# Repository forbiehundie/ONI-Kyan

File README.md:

# ONI-Kyan
A smol 30% columnar stagger keyboard designed to be used with a Pro-Micro and compatibles. 

ONI-Kyan MKI; mx only

ONI-Kyan Shakotan MKI; choc only with choc specific switch spacing

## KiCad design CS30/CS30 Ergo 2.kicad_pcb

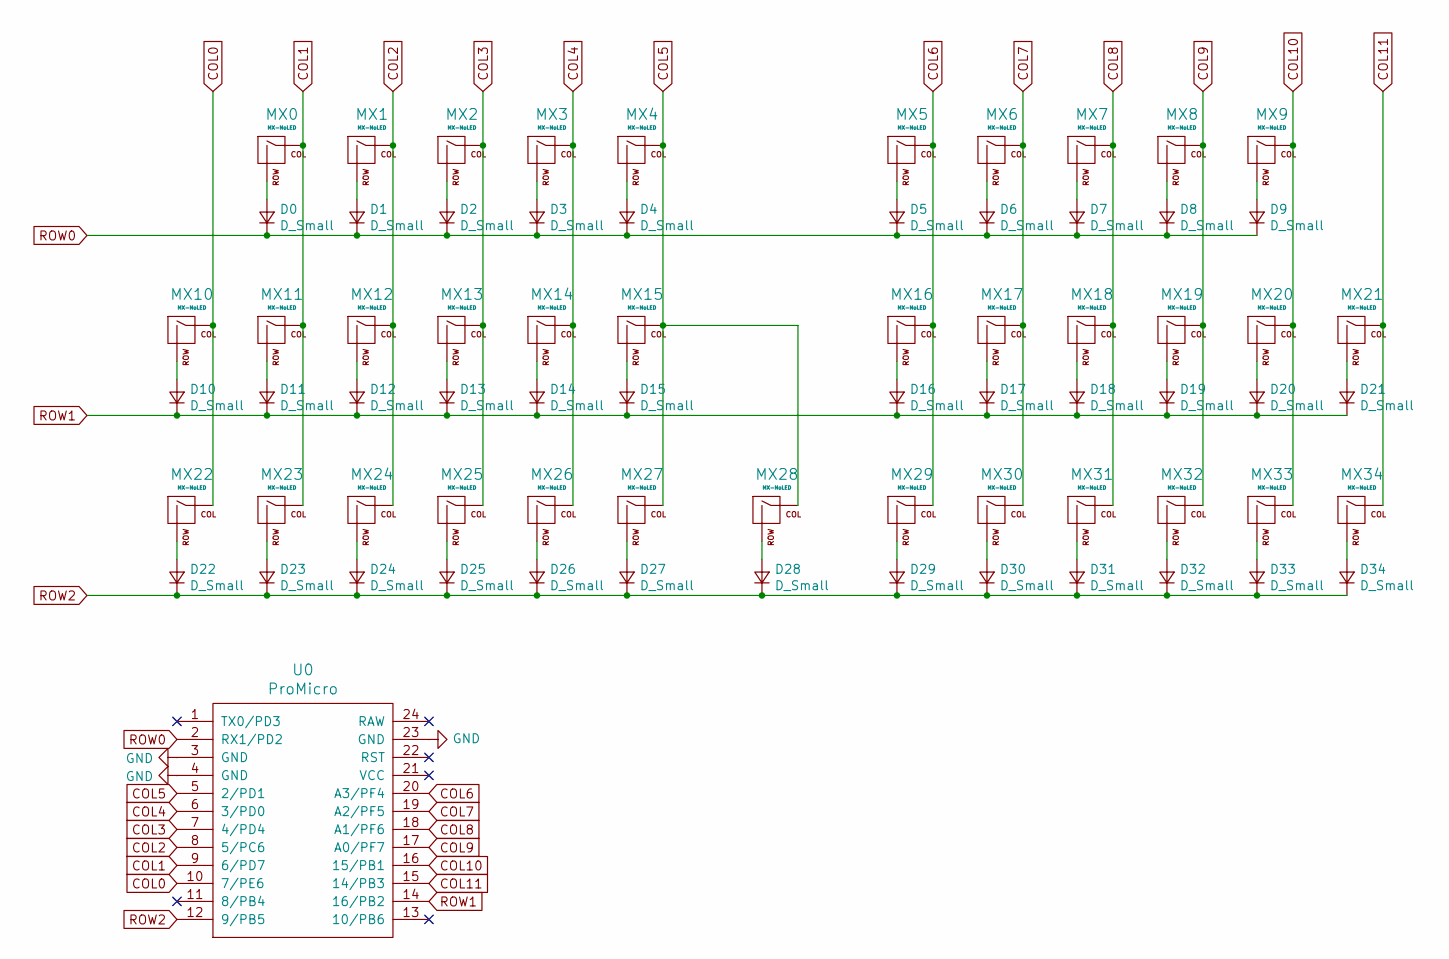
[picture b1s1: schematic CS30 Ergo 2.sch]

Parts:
D0, D1, D2, D3, D4, D5, D6, D7, D8, D9, D10, D11, D12, D13, D14, D15, D16, D17, D18, D19, D20, D21, D22, D23, D24, D25, D26, D27, D28, D29, D30, D31, D32, D33, D34: D_Small; D_SOD-123-Pretty
MX0, MX1, MX2, MX3, MX4, MX5, MX6, MX7, MX8, MX9, MX10, MX11, MX12, MX13, MX14, MX15, MX16, MX17, MX18, MX19, MX20, MX21, MX22, MX23, MX24, MX25, MX26, MX27, MX29, MX30, MX31, MX32, MX33, MX34: MX-NoLED; MXOnly-1U-NoLED
MX28: MX-NoLED; MXOnly-1.25U-NoLED
U0: ProMicro; ArduinoProMicro

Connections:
COL0: MX10.1 (COL), MX22.1 (COL), U0.10 (7/PE6)
COL1: MX0.1 (COL), MX11.1 (COL), MX23.1 (COL), U0.9 (6/PD7)
COL2: MX1.1 (COL), MX12.1 (COL), MX24.1 (COL), U0.8 (5/PC6)
COL3: MX2.1 (COL), MX13.1 (COL), MX25.1 (COL), U0.7 (4/PD4)
COL4: MX3.1 (COL), MX14.1 (COL), MX26.1 (COL), U0.6 (3/PD0)
COL5: MX4.1 (COL), MX15.1 (COL), MX27.1 (COL), MX28.1 (COL), U0.5 (2/PD1)
COL6: MX5.1 (COL), MX16.1 (COL), MX29.1 (COL), U0.20 (A3/PF4)
COL7: MX6.1 (COL), MX17.1 (COL), MX30.1 (COL), U0.19 (A2/PF5)
COL8: MX7.1 (COL), MX18.1 (COL), MX31.1 (COL), U0.18 (A1/PF6)
COL9: MX8.1 (COL), MX19.1 (COL), MX32.1 (COL), U0.17 (A0/PF7)
COL10: MX9.1 (COL), MX20.1 (COL), MX33.1 (COL), U0.16 (15/PB1)
COL11: MX21.1 (COL), MX34.1 (COL), U0.15 (14/PB3)
GND: U0.3 (GND), U0.4 (GND), U0.23 (GND)
unnamed: D0.2 (A), MX0.2 (ROW)
unnamed: D1.2 (A), MX1.2 (ROW)
unnamed: D2.2 (A), MX2.2 (ROW)
unnamed: D3.2 (A), MX3.2 (ROW)
unnamed: D4.2 (A), MX4.2 (ROW)
unnamed: D5.2 (A), MX5.2 (ROW)
unnamed: D6.2 (A), MX6.2 (ROW)
unnamed: D7.2 (A), MX7.2 (ROW)
unnamed: D8.2 (A), MX8.2 (ROW)
unnamed: D9.2 (A), MX9.2 (ROW)
unnamed: D10.2 (A), MX10.2 (ROW)
unnamed: D11.2 (A), MX11.2 (ROW)
unnamed: D12.2 (A), MX12.2 (ROW)
unnamed: D13.2 (A), MX13.2 (ROW)
unnamed: D14.2 (A), MX14.2 (ROW)
unnamed: D15.2 (A), MX15.2 (ROW)
unnamed: D16.2 (A), MX16.2 (ROW)
unnamed: D17.2 (A), MX17.2 (ROW)
unnamed: D18.2 (A), MX18.2 (ROW)
unnamed: D19.2 (A), MX19.2 (ROW)
unnamed: D20.2 (A), MX20.2 (ROW)
unnamed: D21.2 (A), MX21.2 (ROW)
unnamed: D22.2 (A), MX22.2 (ROW)
unnamed: D23.2 (A), MX23.2 (ROW)
unnamed: D24.2 (A), MX24.2 (ROW)
unnamed: D25.2 (A), MX25.2 (ROW)
unnamed: D26.2 (A), MX26.2 (ROW)
unnamed: D27.2 (A), MX27.2 (ROW)
unnamed: D28.2 (A), MX28.2 (ROW)
unnamed: D29.2 (A), MX29.2 (ROW)
unnamed: D30.2 (A), MX30.2 (ROW)
unnamed: D31.2 (A), MX31.2 (ROW)
unnamed: D32.2 (A), MX32.2 (ROW)
unnamed: D33.2 (A), MX33.2 (ROW)
unnamed: D34.2 (A), MX34.2 (ROW)
ROW0: D0.1 (K), D1.1 (K), D2.1 (K), D3.1 (K), D4.1 (K), D5.1 (K), D6.1 (K), D7.1 (K), D8.1 (K), D9.1 (K), U0.2 (RX1/PD2)
ROW1: D10.1 (K), D11.1 (K), D12.1 (K), D13.1 (K), D14.1 (K), D15.1 (K), D16.1 (K), D17.1 (K), D18.1 (K), D19.1 (K), D20.1 (K), D21.1 (K), U0.14 (16/PB2)
ROW2: D22.1 (K), D23.1 (K), D24.1 (K), D25.1 (K), D26.1 (K), D27.1 (K), D28.1 (K), D29.1 (K), D30.1 (K), D31.1 (K), D32.1 (K), D33.1 (K), D34.1 (K), U0.12 (9/PB5)

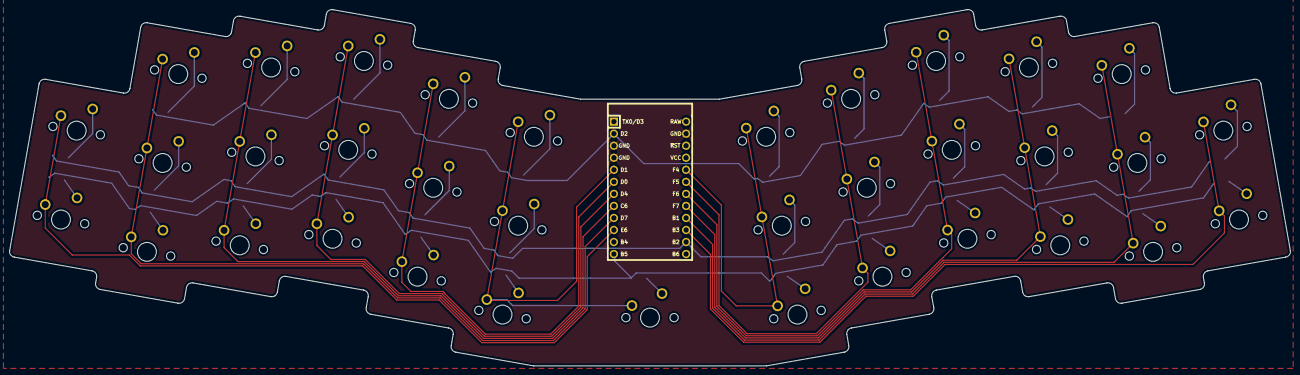
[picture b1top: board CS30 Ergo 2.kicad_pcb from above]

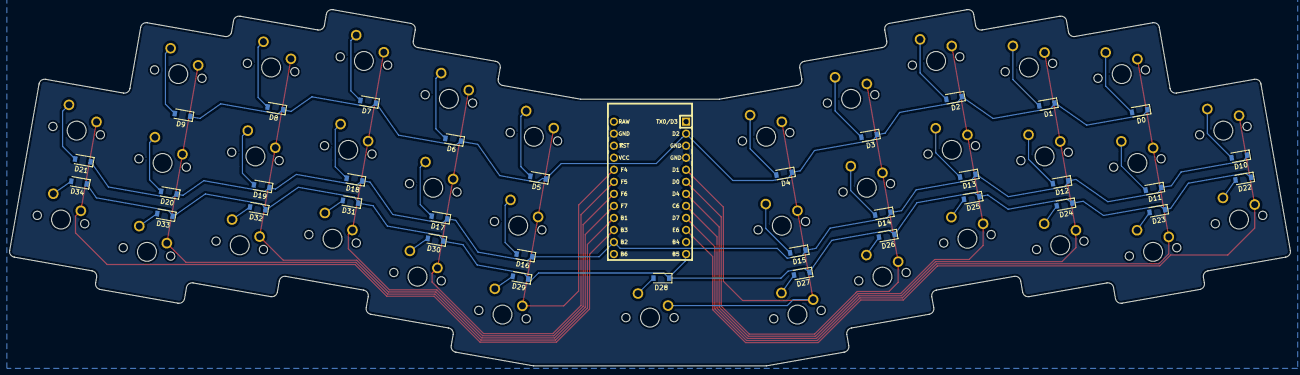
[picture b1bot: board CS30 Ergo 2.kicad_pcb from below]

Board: 2 copper layers, 270.3 x 75.2 mm, 71 parts (35 on the bottom side), 51 nets.

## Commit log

2020-12-10 Initialized project, schematic, and pcb
2020-12-12 Initalized Ergo PCB
2020-12-14 Created Test Gerber
2020-12-15 Routed CS35 variant
2021-01-04 Rerouted Ergo and created test gerbers
2021-01-09 Created CS30 Ergo 3, OniKyan
2021-01-10 Finalized ONI-Kyan MK-I
    Created gerbers and ordered prototypes through JLCPCB
2021-01-21 Gerbolyze test
2021-01-22 Added initial QMK firmware
2021-01-22 Reorganization of repo
2021-01-22 Moved firmware folder
2021-01-22 Organization
2021-01-22 Repo organization
2021-01-22 Create LICENSE
2021-02-15 Added ONI-Kyan Shakotan MKI
2021-02-25 Added a picture
